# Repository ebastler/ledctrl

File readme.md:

# ledctrl
This project was born with the idea of creating a simple and efficient way of controlling an RGB, one WW/CW and an additional aux stripe from a single smart-home capable controller. Then feature creep happened, and here we are.

The PCB uses a modern and power-efficient RISC-V based ESP32C6 and features a step-down converter to supply the 5V logic, as well as an LDO for the 3.3V logic. The Aux channel has a separate supply input from the other 5 channels, and both supply domains can be used for 12V or 24V stripes, not necessarily the same voltage at the same time. The logic supply is generated from either of the two supply channels, which are ORed together with diodes.

2 inputs for external buttons can be used to directly control the LEDs, or send commands via MQTT. I also added headers for the most common breakout boards for a bunch of different environmental sensors. 

While programming over USB works without issues for ESP32C6, I also added a UART header as a fallback, for debugging or just for use as another GPIO breakout.

### Features:
* Up to 5+1 channels of 12V or 24V LED stripes
* ESP32C6
* USB-C for programming
* Dim onboard LEDs to indicate status of each PWM channel, as well as both input power domains
* WS2812B LED onboard as a status indicator/for devboard use
* Almost all unused GPIOs are available on headers
* Headers for BME280, SCD40 and SGP40 environment sensors
* 2 inputs for pushbuttons/switches

### Software
The board is mainly made for use with [Tasmota](https://github.com/arendst/tasmota), and currently only supported using the `tasmota32c6cdc` firmware, taken off the `13.3.0.1` development branch. Stable versions have not yet added support for this chip. A template that can make use of most features will be published at a later point, once I finalized my firmware setup.

### Pictures

## Thanks
* arendst and the whole community of Tasmota contributors for their excellent firmware
* [MarvFPV](https://github.com/marvfpv) who surprisingly did not get upset about me sending updates of new revisions with minimal changes every other day asking for his opinion

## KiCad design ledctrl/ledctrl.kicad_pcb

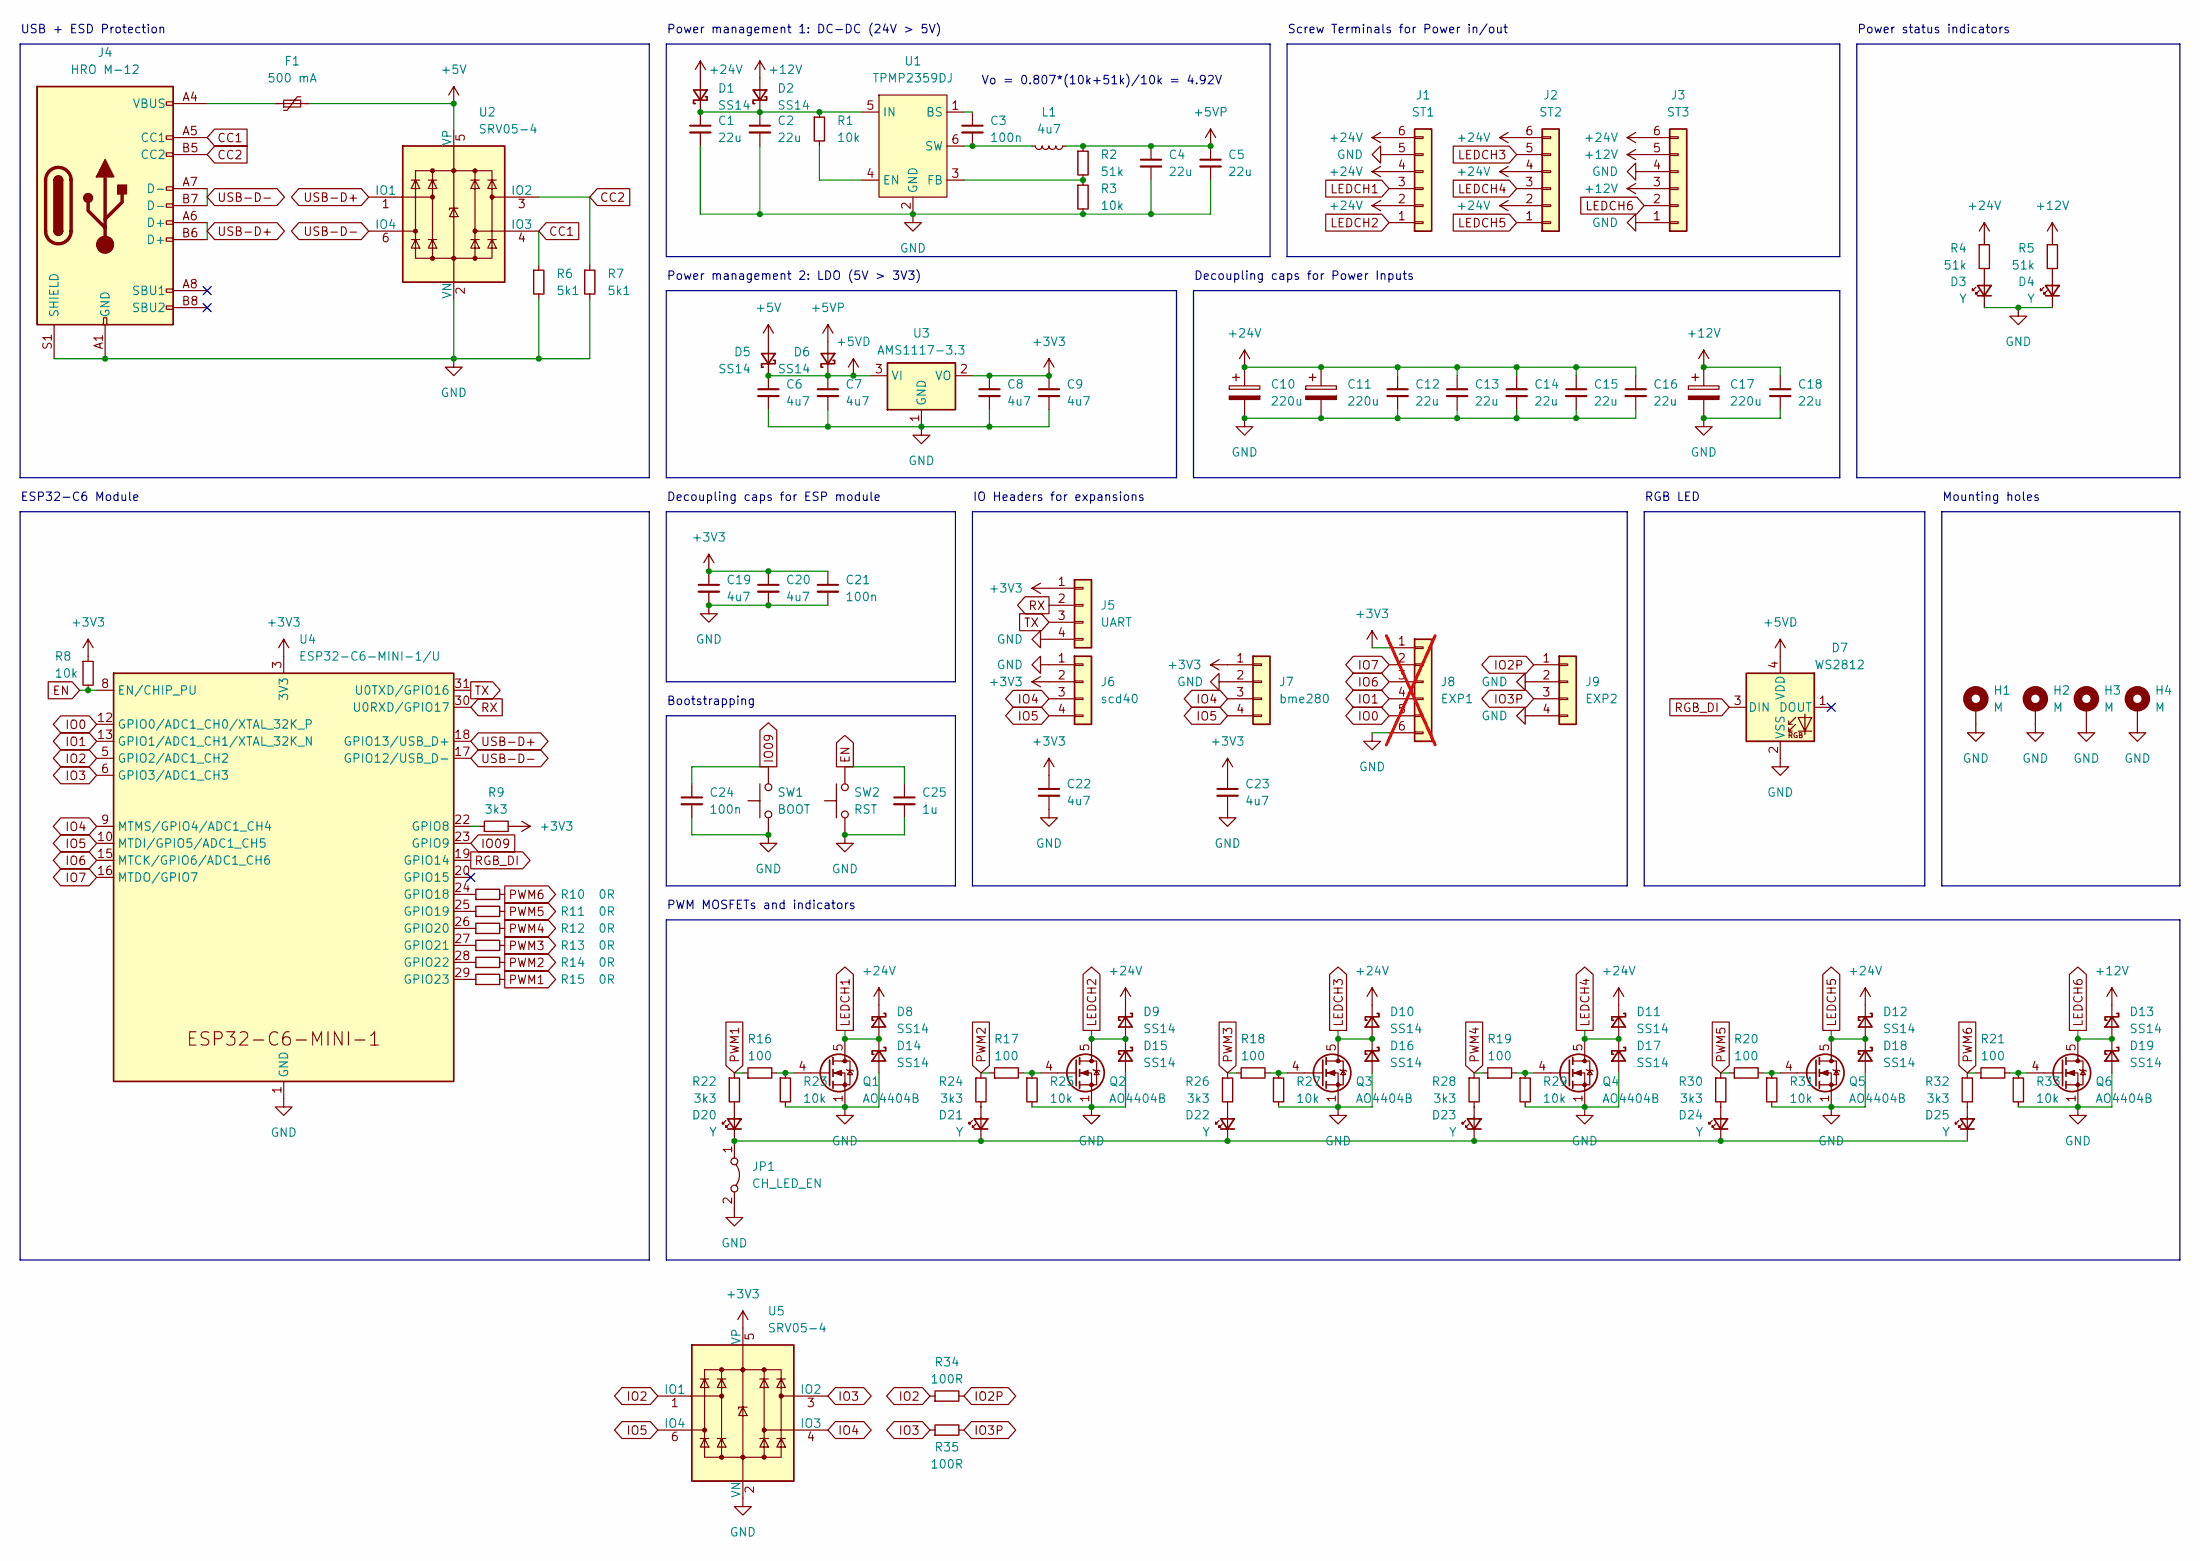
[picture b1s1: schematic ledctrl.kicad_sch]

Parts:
C1, C2, C4, C5, C12, C13, C14, C15, C16, C18: 22u; C_0805_2012Metric; LCSC C6119901
C3, C21, C24: 100n; C_0402_1005Metric
C6, C7, C8, C9, C19, C20, C22, C23: 4u7; C_0402_1005Metric
C10, C11, C17: 220u; CP_Elec_8x10; LCSC C278406
C25: 1u; C_0402_1005Metric
D1, D2, D5, D6, D8, D9, D10, D11, D12, D13, D14, D15, D16, D17, D18, D19: SS14; D_SMA
D3, D4, D20, D21, D22, D23, D24, D25: Y; LED_0603_1608Metric; LCSC C72038
D7: WS2812; LED_WS2812_2020
F1: 500 mA; Fuse_0603_1608Metric
H1, H2, H3, H4: M; MountingHole_3.2mm_M3_Pad_Via
J1: ST1; TerminalBlock_Ningbo_Kangnex _WJ128V-5.0-6P_1x06_P5.00mm_Ho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; LCSC C192771
J2: ST2; TerminalBlock_Ningbo_Kangnex _WJ128V-5.0-6P_1x06_P5.00mm_Ho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; LCSC C192771
J3: ST3; TerminalBlock_Ningbo_Kangnex _WJ128V-5.0-6P_1x06_P5.00mm_Ho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; LCSC C192771
J4: HRO M-12; USB_C_Receptacle_HRO_TYPE-C-31-M-12
J5: UART; PinHeader_1x04_P2.54mm_Vertical
J6: scd40; PinHeader_1x04_P2.54mm_Vertical
J7: bme280; PinHeader_1x04_P2.54mm_Vertical
J8: EXP1; PinHeader_1x06_P2.54mm_Vertical; not fitted
J9: EXP2; TerminalBlock_DIBO_DB125-3.5-4P-GN-S_1x04_P3.50mm_Horizontal; LCSC C2757925
JP1: CH_LED_EN; SolderJumper-2_P1.3mm_Bridged_RoundedPad1.0x1.5mm
L1: 4u7; L_Changjiang_FNR3012S; LCSC C528014
Q1, Q2, Q3, Q4, Q5, Q6: AO4404B; SOIC-8_3.9x4.9mm_P1.27mm
R1, R3, R8, R23, R25, R27, R29, R31, R33: 10k; R_0402_1005Metric
R2, R4, R5: 51k; R_0402_1005Metric
R6, R7: 5k1; R_0402_1005Metric
R9, R22, R24, R26, R28, R30, R32: 3k3; R_0402_1005Metric
R10, R11, R12, R13, R14, R15: 0R; R_0402_1005Metric; LCSC C17168
R16, R17, R18, R19, R20, R21: 100; R_0402_1005Metric
R34, R35: 100R; R_0402_1005Metric; LCSC C17168
SW1: BOOT; SW_T1A2QR
SW2: RST; SW_T1A2QR
U1: TPMP2359DJ; SOT-23-6
U2, U5: SRV05-4; SOT-23-6-routable
U3: AMS1117-3.3; SOT-223-3_TabPin2
U4: ESP32-C6-MINI-1/U; ESP32-C6-MINI-1

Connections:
+3V3: C8.1, C9.1, C19.1, C20.1, C21.1, C22.1, C23.1, J5.1, J6.2, J7.1, J8.1, R8.1, R9.2, U3.2 (VO), U4.3 (3V3), U5.5 (VP)
+5V: D5.2 (A), F1.2, U2.5 (VP)
+5VD: C6.1, C7.1, D5.1 (K), D6.1 (K), D7.4 (VDD), U3.3 (VI)
+5VP: C4.1, C5.1, D6.2 (A), L1.1, R2.1
+12V: C17.1, C18.1, D2.2 (A), D13.1 (K), J3.3, J3.5, R5.1
+24V: C10.1, C11.1, C12.1, C13.1, C14.1, C15.1, C16.1, D1.2 (A), D8.1 (K), D9.1 (K), D10.1 (K), D11.1 (K), D12.1 (K), J1.2, J1.4, J1.6, J2.2, J2.4, J2.6, J3.6, R4.1
CC1: J4.A5 (CC1), R6.1, U2.4 (IO3)
CC2: J4.B5 (CC2), R7.1, U2.3 (IO2)
EN: C25.1, R8.2, SW2.2, U4.8 (EN/CHIP_PU)
GND: C1.2, C2.2, C4.2, C5.2, C6.2, C7.2, C8.2, C9.2, C10.2, C11.2, C12.2, C13.2, C14.2, C15.2, C16.2, C17.2, C18.2, C19.2, C20.2, C21.2, C22.2, C23.2, C24.2, C25.2, D3.1 (K), D4.1 (K), D7.2 (VSS), D14.2 (A), D15.2 (A), D16.2 (A), D17.2 (A), D18.2 (A), D19.2 (A), H1.1, H2.1, H3.1, H4.1, J1.5, J3.1, J3.4, J4.A1 (GND), J4.A12 (GND), J4.B1 (GND), J4.B12 (GND), J4.S1 (SHIELD), J5.4, J6.1, J7.2, J8.6, J9.2, J9.4, JP1.2 (B), Q1.1 (S), Q1.2 (S), Q1.3 (S), Q2.1 (S), Q2.2 (S), Q2.3 (S), Q3.1 (S), Q3.2 (S), Q3.3 (S), Q4.1 (S), Q4.2 (S), Q4.3 (S), Q5.1 (S), Q5.2 (S), Q5.3 (S), Q6.1 (S), Q6.2 (S), Q6.3 (S), R3.2, R6.2, R7.2, R23.2, R25.2, R27.2, R29.2, R31.2, R33.2, SW1.1, SW2.1, U1.2 (GND), U2.2 (VN), U3.1 (GND), U4.1 (GND), U4.2 (GND), U4.11 (GND), U4.14 (GND), U4.36 (GND), U4.37 (GND), U4.38 (GND), U4.39 (GND), U4.40 (GND), U4.41 (GND), U4.42 (GND), U4.43 (GND), U4.44 (GND), U4.45 (GND), U4.46 (GND), U4.47 (GND), U4.48 (GND), U4.49 (GND), U4.50 (GND), U4.51 (GND), U4.52 (GND), U4.53 (GND), U5.2 (VN)
IO0: J8.5, U4.12 (GPIO0/ADC1_CH0/XTAL_32K_P)
IO1: J8.4, U4.13 (GPIO1/ADC1_CH1/XTAL_32K_N)
IO2: R34.1, U4.5 (GPIO2/ADC1_CH2), U5.1 (IO1)
IO2P: J9.1, R34.2
IO3: R35.1, U4.6 (GPIO3/ADC1_CH3), U5.3 (IO2)
IO3P: J9.3, R35.2
IO4: J6.3, J7.3, U4.9 (MTMS/GPIO4/ADC1_CH4), U5.4 (IO3)
IO5: J6.4, J7.4, U4.10 (MTDI/GPIO5/ADC1_CH5), U5.6 (IO4)
IO6: J8.3, U4.15 (MTCK/GPIO6/ADC1_CH6)
IO7: J8.2, U4.16 (MTDO/GPIO7)
IO09: C24.1, SW1.2, U4.23 (GPIO9)
LEDCH1: D8.2 (A), D14.1 (K), J1.3, Q1.5 (D), Q1.6 (D), Q1.7 (D), Q1.8 (D)
LEDCH2: D9.2 (A), D15.1 (K), J1.1, Q2.5 (D), Q2.6 (D), Q2.7 (D), Q2.8 (D)
LEDCH3: D10.2 (A), D16.1 (K), J2.5, Q3.5 (D), Q3.6 (D), Q3.7 (D), Q3.8 (D)
LEDCH4: D11.2 (A), D17.1 (K), J2.3, Q4.5 (D), Q4.6 (D), Q4.7 (D), Q4.8 (D)
LEDCH5: D12.2 (A), D18.1 (K), J2.1, Q5.5 (D), Q5.6 (D), Q5.7 (D), Q5.8 (D)
LEDCH6: D13.2 (A), D19.1 (K), J3.2, Q6.5 (D), Q6.6 (D), Q6.7 (D), Q6.8 (D)
unnamed: C1.1, C2.1, D1.1 (K), D2.1 (K), R1.1, U1.5 (IN)
unnamed: D3.2 (A), R4.2
unnamed: D4.2 (A), R5.2
unnamed: D20.2 (A), R22.2
unnamed: D20.1 (K), D21.1 (K), D22.1 (K), D23.1 (K), D24.1 (K), D25.1 (K), JP1.1 (A)
unnamed: D21.2 (A), R24.2
unnamed: D22.2 (A), R26.2
unnamed: D23.2 (A), R28.2
unnamed: D24.2 (A), R30.2
unnamed: D25.2 (A), R32.2
unnamed: F1.1, J4.A4 (VBUS), J4.A9 (VBUS), J4.B4 (VBUS), J4.B9 (VBUS)
unnamed: Q1.4 (G), R16.2, R23.1
unnamed: Q2.4 (G), R17.2, R25.1
unnamed: Q3.4 (G), R18.2, R27.1
unnamed: Q4.4 (G), R19.2, R29.1
unnamed: Q5.4 (G), R20.2, R31.1
unnamed: Q6.4 (G), R21.2, R33.1
unnamed: C3.1, U1.1 (BS)
unnamed: R1.2, U1.4 (EN)
unnamed: R2.2, R3.1, U1.3 (FB)
unnamed: C3.2, L1.2, U1.6 (SW)
unnamed: R9.1, U4.22 (GPIO8)
unnamed: R10.1, U4.24 (GPIO18)
unnamed: R11.1, U4.25 (GPIO19)
unnamed: R12.1, U4.26 (GPIO20)
unnamed: R13.1, U4.27 (GPIO21)
unnamed: R14.1, U4.28 (GPIO22)
unnamed: R15.1, U4.29 (GPIO23)
PWM1: R15.2, R16.1, R22.1
PWM2: R14.2, R17.1, R24.1
PWM3: R13.2, R18.1, R26.1
PWM4: R12.2, R19.1, R28.1
PWM5: R11.2, R20.1, R30.1
PWM6: R10.2, R21.1, R32.1
RGB_DI: D7.3 (DIN), U4.19 (GPIO14)
RX: J5.2, U4.30 (U0RXD/GPIO17)
TX: J5.3, U4.31 (U0TXD/GPIO16)
USB-D+: J4.A6 (D+), J4.B6 (D+), U2.1 (IO1), U4.18 (GPIO13/USB_D+)
USB-D-: J4.A7 (D-), J4.B7 (D-), U2.6 (IO4), U4.17 (GPIO12/USB_D-)

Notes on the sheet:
IO Headers for expansions
Vo = 0.807*(10k+51k)/10k = 4.92V
Bootstrapping
Power management 2: LDO (5V > 3V3)
Screw Terminals for Power in/out
Mounting holes
Power management 1: DC-DC (24V > 5V)
USB + ESD Protection
Decoupling caps for ESP module
ESP32-C6 Module
Decoupling caps for Power Inputs
Power status indicators
RGB LED
PWM MOSFETs and indicators

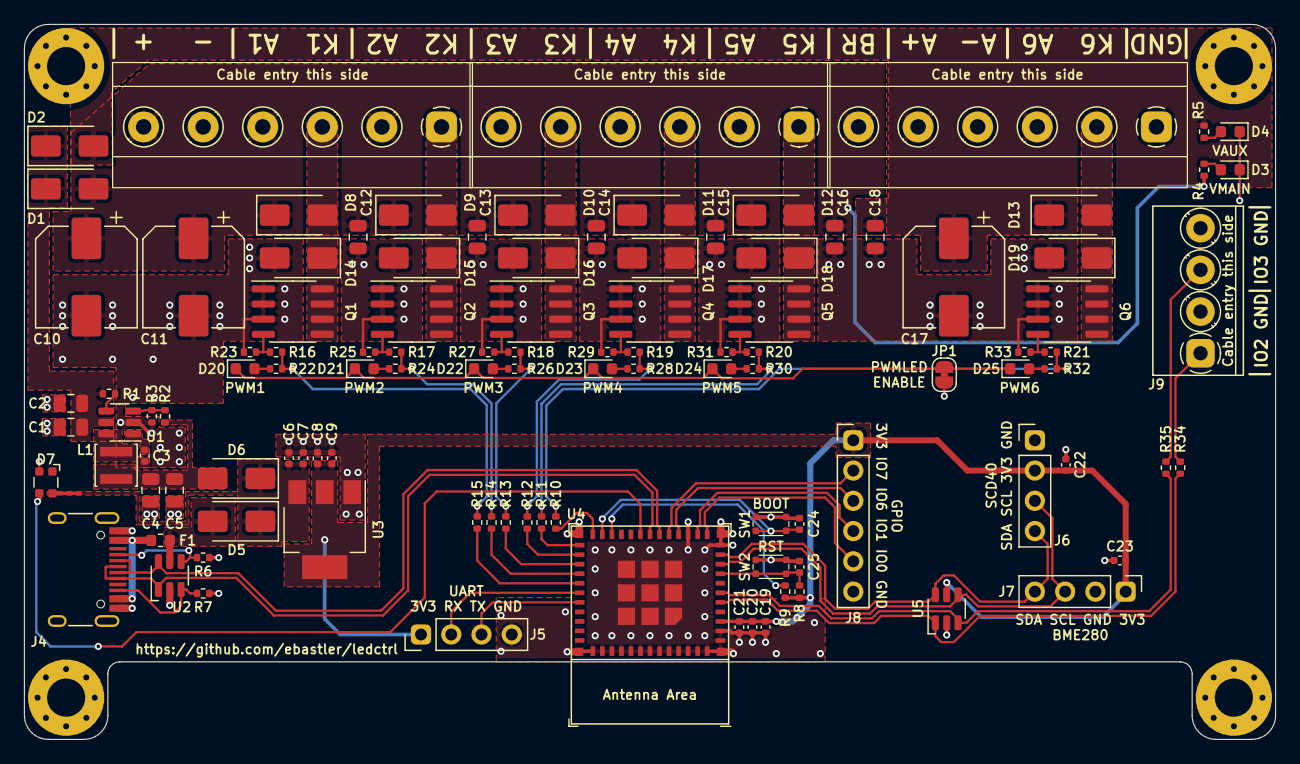
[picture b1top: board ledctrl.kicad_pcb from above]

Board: 2 copper layers, 105.0 x 60.0 mm, 114 parts (0 on the bottom side), 66 nets.

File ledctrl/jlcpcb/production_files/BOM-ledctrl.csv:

Comment,Designator,Footprint,LCSC
BOOT,"SW1,SW2",SW_T1A2QR,C100056
AO4404B,"Q1,Q2,Q3,Q4,Q5,Q6",SOIC-8_3.9x4.9mm_P1.27mm,C115829
HRO M-12,J4,USB_C_Receptacle_HRO_TYPE-C-31-M-12,C165948
0R,"R10,R11,R12,R13,R14,R15,R34,R35",R_0402_1005Metric,C17168
ST1,"J1,J2,J3",TerminalBlock_Ningbo_Kangnex _WJ128V-5.0-6P_1x06_P5.00mm_Horizontal,C192771
500 mA,F1,Fuse_0603_1608Metric,C20789
4u7,"C19,C20,C22,C23,C6,C7,C8,C9",C_0402_1005Metric,C23733
SS14,"D1,D10,D11,D12,D13,D14,D15,D16,D17,D18,D19,D2,D5,D6,D8,D9",D_SMA,C2480
100,"R16,R17,R18,R19,R20,R21",R_0402_1005Metric,C25076
10k,"R1,R23,R25,R27,R29,R3,R31,R33,R8",R_0402_1005Metric,C25744
51k,"R2,R4,R5",R_0402_1005Metric,C25794
3k3,"R22,R24,R26,R28,R30,R32,R9",R_0402_1005Metric,C25890
5k1,"R6,R7",R_0402_1005Metric,C25905
UART,"J5,J6,J7",PinHeader_1x04_P2.54mm_Vertical,C2691448
EXP2,J9,TerminalBlock_DIBO_DB125-3.5-4P-GN-S_1x04_P3.50mm_Horizontal,C2757925
220u,"C10,C11,C17",CP_Elec_8x10,C278406
TPMP2359DJ,U1,SOT-23-6,C2959845
100n,"C21,C24,C3",C_0402_1005Metric,C307331
4u7,L1,L_Changjiang_FNR3012S,C528014
1u,C25,C_0402_1005Metric,C52923
ESP32-C6-MINI-1/U,U4,ESP32-C6-MINI-1,C5736265
22u,"C1,C12,C13,C14,C15,C16,C18,C2,C4,C5",C_0805_2012Metric,C6119901
AMS1117-3.3,U3,SOT-223-3_TabPin2,C6186
Y,"D20,D21,D22,D23,D24,D25,D3,D4",LED_0603_1608Metric,C72038
SRV05-4,"U2,U5",SOT-23-6-routable,C85364
WS2812,D7,LED_WS2812_2020,C965555

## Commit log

2023-12-29 removed .csv from gitignore for BOM/POS files
2023-12-29 add license
2023-12-29 added readme
2023-12-29 initial commit of kicad project files
2024-10-02 moved T1A2QR from local lib to marbastlib
